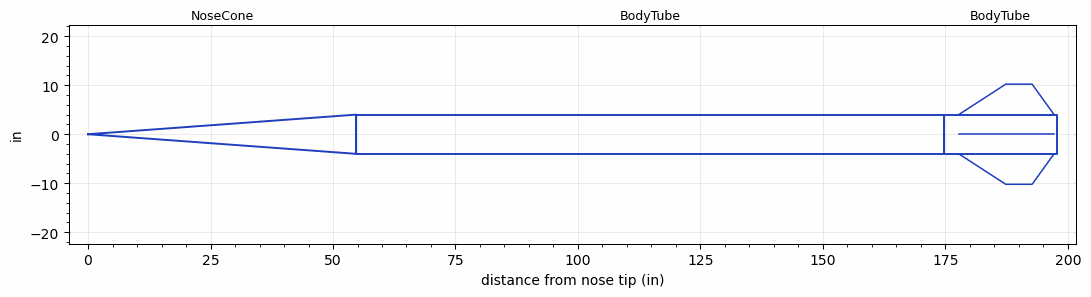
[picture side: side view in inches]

<RASAeroDocument>
 <FileVersion>2</FileVersion>
 <RocketDesign>
  <NoseCone>
   <Length>54.7243</Length>
   <Diameter>8</Diameter>
   <Shape>Conical</Shape>
   <Location>0</Location>
  </NoseCone>
  <BodyTube>
   <Length>119.9998</Length>
   <Diameter>8</Diameter>
   <Location>54.7243</Location>
  </BodyTube>
  <BodyTube>
   <Length>23</Length>
   <Diameter>8</Diameter>
   <Location>174.7241</Location>
   <Fin>
    <Count>4</Count>
    <Chord>19.4635</Chord>
    <Span>6.2205</Span>
    <SweepDistance>9.6063</SweepDistance>
    <TipChord>5.374</TipChord>
    <Thickness>0.25</Thickness>
    <Location>20.0147</Location>
    <AirfoilSection>Square</AirfoilSection>
   </Fin>
  </BodyTube>
  <Surface>Rough Camouflage Paint</Surface>
  <CD>0</CD>
  <ModifiedBarrowman>False</ModifiedBarrowman>
  <Turbulence>False</Turbulence>
  <UseBooster1>False</UseBooster1>
  <UseBooster2>False</UseBooster2>
  <Comments>Testing for stability --&gt; upthrust sim</Comments>
 </RocketDesign>
 <LaunchSite>
  <Altitude>0</Altitude>
  <Pressure>29.9214</Pressure>
  <RodAngle>0</RodAngle>
  <RodLength>3.2808</RodLength>
  <Temperature>59</Temperature>
  <WindSpeed>4.4739</WindSpeed>
 </LaunchSite>
 <Recovery>
  <Altitude1>0</Altitude1>
  <Altitude2>0</Altitude2>
  <DeviceType1>None</DeviceType1>
  <DeviceType2>None</DeviceType2>
  <Event1>False</Event1>
  <Event2>False</Event2>
  <Size1>0</Size1>
  <Size2>0</Size2>
  <EventType1>None</EventType1>
  <EventType2>None</EventType2>
  <CD1>0</CD1>
  <CD2>0</CD2>
 </Recovery>
 <SimulationList>
  <Simulation>
   <SustainerLaunchWt>107.7775</SustainerLaunchWt>
   <SustainerCG>125.7122</SustainerCG>
   <SustainerIgnitionDelay>0</SustainerIgnitionDelay>
   <Booster1SeparationDelay>0</Booster1SeparationDelay>
   <Booster1IgnitionDelay>0</Booster1IgnitionDelay>
   <IncludeBooster1>False</IncludeBooster1>
   <Booster2Delay>0</Booster2Delay>
   <IncludeBooster2>False</IncludeBooster2>
  </Simulation>
 </SimulationList>
</RASAeroDocument>
